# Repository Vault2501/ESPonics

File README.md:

# ESPonics
ESPonics is a ESP32 based automated Aeroponics system. It consists of fan, light and pump control as well as sensors for temperature, humidity, water level, ph and ec and is controlled via a web interface.

# Status
This is still WIP

Done:
* Pump control
* Fan Control
* Light Control
* Test Web UI

Current WIP:
* Sensors
* Case models

Todo:
* Userfriendly UI
* Parameter configuration
* Automatic control
* PCB

# Documentation
Documentation will go to the documentaiton folder

# Media
Photos and Videos of this project can be found here:
* Grow and feeding container with pumps: https://pixel.tchncs.de/i/web/post/594626511061922875
* WIP main controller,sensor and light/fan modules: https://pixel.tchncs.de/i/web/post/594629490395300993
* Finished prototype modules: https://pixel.tchncs.de/i/web/post/597583425622062798
* Video testing the pumps: https://makertube.net/w/gAhuFigTPs9yXAJNz8wZ4G

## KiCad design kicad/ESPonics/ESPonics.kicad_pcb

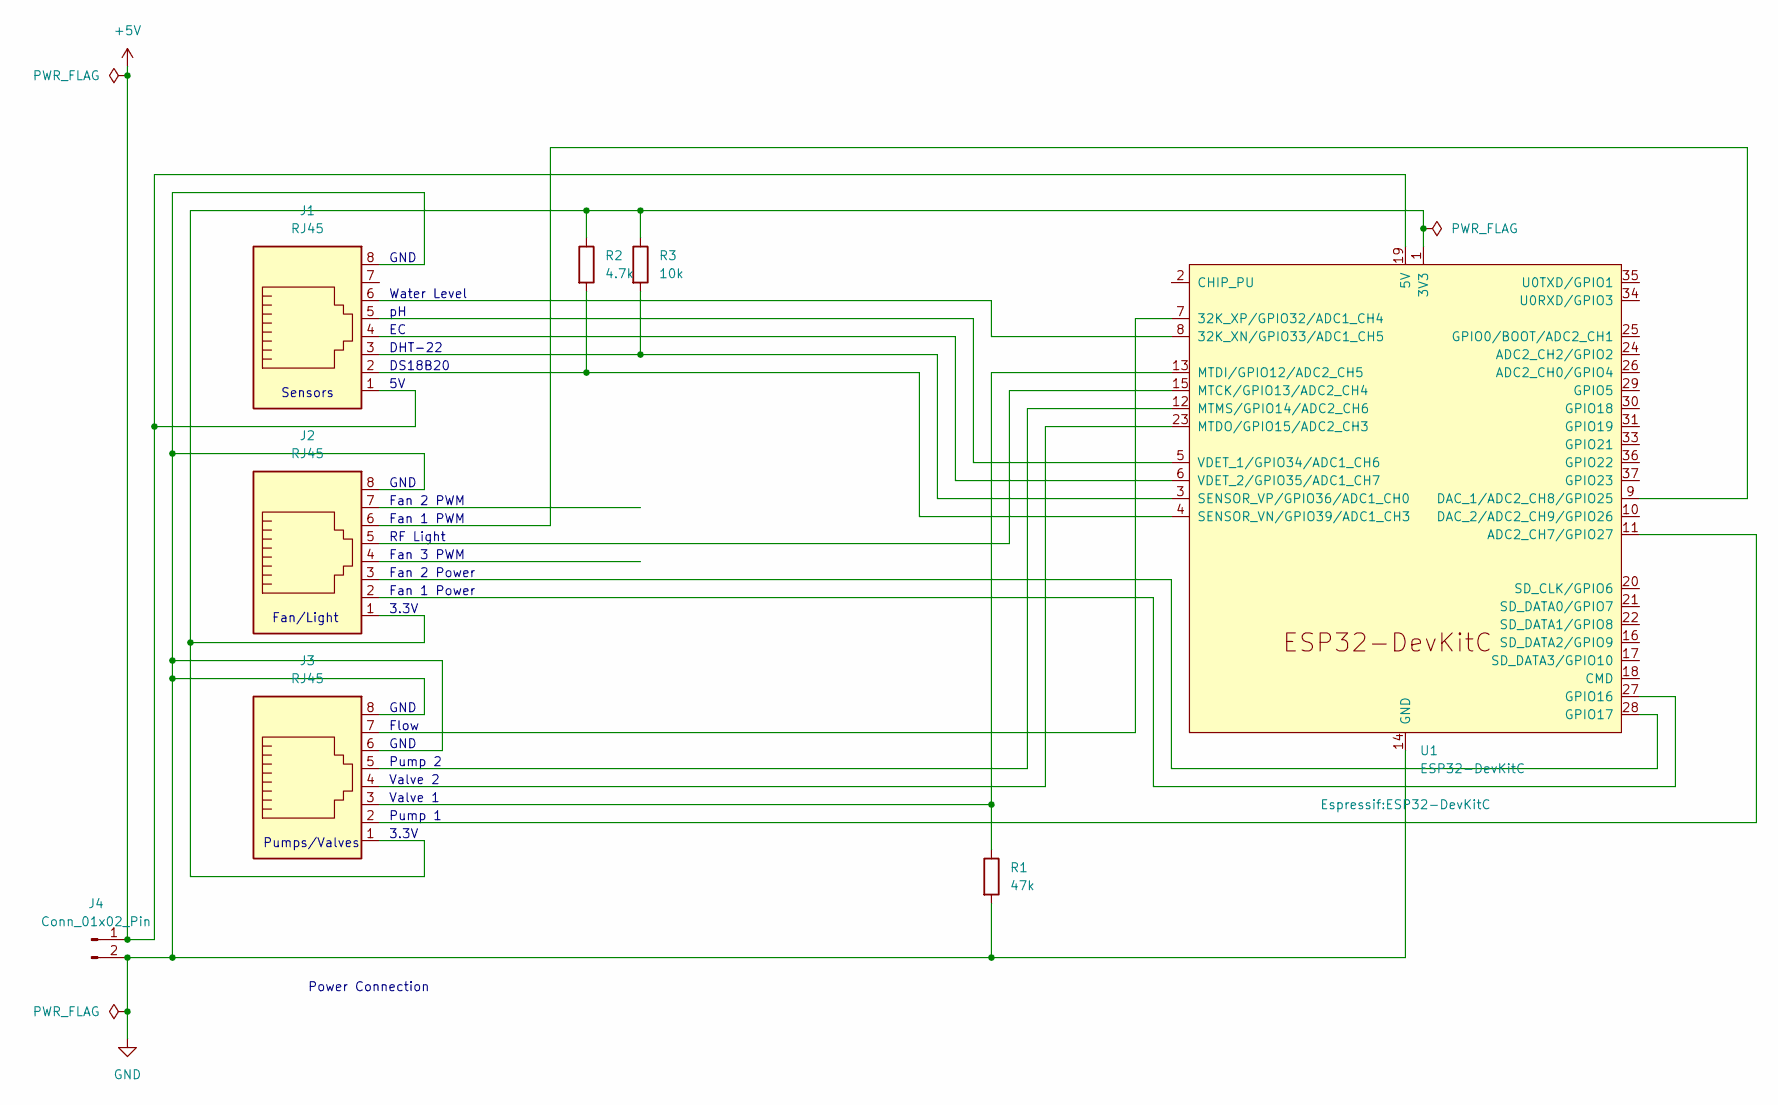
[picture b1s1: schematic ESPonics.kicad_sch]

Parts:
J1, J3: RJ45; RJ45_Amphenol_54602-x08_Horizontal
J2: RJ45
J4: Conn_01x02_Pin; JST_XH_B2B-XH-A_1x02_P2.50mm_Vertical
R1: 47k
R2: 4.7k; R_Axial_DIN0204_L3.6mm_D1.6mm_P1.90mm_Vertical
R3: 10k; R_Axial_DIN0204_L3.6mm_D1.6mm_P1.90mm_Vertical
U1: ESP32-DevKitC

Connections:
+5V: J1.1, J4.1, U1.19 (5V)
GND: J1.8, J2.8, J3.6, J3.8, J4.2, R1.2, U1.14 (GND), U1.32 (GND), U1.38 (GND)
unnamed: J2.1, J3.1, R2.1, R3.1, U1.1 (3V3)
unnamed: J1.6, U1.8 (32K_XN/GPIO33/ADC1_CH5)
unnamed: J3.7, U1.7 (32K_XP/GPIO32/ADC1_CH4)
unnamed: J3.2, U1.11 (ADC2_CH7/GPIO27)
unnamed: J2.6, U1.9 (DAC_1/ADC2_CH8/GPIO25)
unnamed: J2.2, U1.27 (GPIO16)
unnamed: J2.3, U1.28 (GPIO17)
unnamed: J2.5, U1.15 (MTCK/GPIO13/ADC2_CH4)
unnamed: J3.3, R1.1, U1.13 (MTDI/GPIO12/ADC2_CH5)
unnamed: J3.4, U1.23 (MTDO/GPIO15/ADC2_CH3)
unnamed: J3.5, U1.12 (MTMS/GPIO14/ADC2_CH6)
unnamed: J1.2, R2.2, U1.4 (SENSOR_VN/GPIO39/ADC1_CH3)
unnamed: J1.3, R3.2, U1.3 (SENSOR_VP/GPIO36/ADC1_CH0)
unnamed: J1.5, U1.5 (VDET_1/GPIO34/ADC1_CH6)
unnamed: J1.4, U1.6 (VDET_2/GPIO35/ADC1_CH7)

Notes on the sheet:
GND
3.3V
DHT-22
Flow
Valve 1
Fan 2 Power
Pump 1
Valve 2
Fan/Light
Power Connection
Water Level
RF Light
Fan 1 Power
Fan 3 PWM
DS18B20
Fan 1 PWM
Pump 2
Fan 2 PWM
Sensors
Pumps/Valves

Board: 2 copper layers, 8 parts (0 on the bottom side), 17 nets, no tracks yet.

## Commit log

2023-07-23 Initial commit - pumps, valves and flow meter works via ws
2023-07-23 Add index.html and wifi.h
2023-07-23 Add light and fan on/off functionality to to arduino code
2023-07-24 Fix typo, add some debug info and make fans and light switch work
2023-07-25 Add Speed control for Fan1 to webUI - still untested
2023-07-25 Add functionality for setting light times - untested
2023-07-25 Fix typo
2023-08-19 Set light to seconds for testing and fix pwm control for fan
2023-08-19 Add openscad case models and stl files
2023-08-19 Add fan adapter openscad model and stl file
2023-08-19 Add filter openscad model and stl files
2023-08-19 Add clip bar and clip openscad model and stl files
2023-08-20 Add first kicad files
2023-08-20 Add .gitignore
2023-08-20 Add bom template
2023-08-20 Add Sensor GPIO definitions
2023-08-20 Add GPIO connections to kicad
2023-08-20 Added openscad-libraries submodule to the project.
2023-08-20 Add main controller case
2023-08-22 Fix the ethernet port fix
2023-08-22 Add dht reder code
2023-08-22 Add temperature reading code
2023-08-22 Add water state sensor reading code
2023-08-22 Update openscad lib module
2023-08-22 Move global variables to separate file
2023-08-23 Create tabs for UI
2023-08-23 Add pull up resistors
2023-08-24 Enlarge usb access opening in main case
2023-08-24 Add calibration subpage
2023-08-24 Add calibration subpage to code
2023-08-24 Start creating first pcb
2023-08-26 Small pcb changes
2023-08-26 Add stl files for 80mm fan adapter and small fixes for openscad model
2023-08-26 Create generic readSensor function
2023-08-26 Fix typos
2023-08-27 Add debug print for easier handling
2023-08-27 Update schematic with new GPIOs
2023-08-27 Add DHT sensor values to ui
2023-08-27 Add remaining sensor data display to ui and mock ph and ec functions
2023-08-27 Change UI title and headline to ESPonics
2023-08-31 Fix water level code and change connected pins.
2023-09-03 Add first calibration code
2023-09-03 Add playground with experiments
2023-09-03 Add more ph functionality
2023-09-03 Use A0 (G39) for ph sensor
2023-09-03 Remove separate calibration page and finish up ph calibration
2023-09-04 Fix seom ph calibration issues
2023-09-04 Adjust pin assignments
2023-09-04 Another pin fix
2023-09-08 Update kicad file
2023-09-08 Clean up formatting
2023-10-03 Add small connector for alu profile bars
2024-04-23 Add wip bom and overview to docs
2024-05-06 Add delay between turning on pump and opening valve
2024-05-06 Cleanup and added comments to variables
2024-05-06 move wifi credentials
2024-05-06 directly use APKEY and remove const vars
2024-05-06 Move wifimanager functions to separate file
2024-05-07 Remove OTA as it does not work
2024-05-07 Start separating static vars into config file and use symbols for them
2024-05-07 Move variables to structures for better overview
2024-05-07 Continue moving vars to structs
2024-05-07 Move ph settings to structs
2024-05-07 Move pin setup to external function
2024-05-09 Create class for ph sensor
2024-05-10 Add tds class
2024-05-10 Make use of ph classe and remove old code
2024-05-12 Add TDS calibration method
2024-05-12 Clean up variables, add debug routines
2024-05-12 Change ph update code
2024-05-12 Cleanup
2024-05-12 Save calibration parameters
2024-05-12 Move sensor read functions to own file and clean up some more
2024-05-12 fix small issues
2024-05-13 Add schematics for fans and light extension
2024-05-14 Add kicad schema for sensors module
2024-05-15 Add pump and valve module schematics
2024-05-15 Add kicad backup folders to gitignore
2024-05-15 Add power converter to pump module schematic
2024-05-16 Add media for documentation
2024-05-17 Read sensors without passing by reference
2024-05-17 Add debug statements to tds
2024-05-17 Small changes to schematics
2024-05-23 Add calibration values to ui and temp compensation for tds
2024-05-23 Add flow variables to structs
2024-08-23 Add new ph code
2024-08-25 Change ph calibration to detect value and prepare for logging
2024-08-25 Add logging tab to webpage and display log messages on it
2024-08-26 Clean up calibration frontend and add log messages to calibration
2024-08-27 Adjust ph range
2024-08-29 Add OTA functionality
2024-08-30 Add time and day functionality
2024-08-30 Add small scripts to easy create html file for edits
2024-08-31 Clean up CSS
2024-08-31 Display date and time in the ui
2024-08-31 Fix bug
2024-08-31 Fix date and time retrieval
2024-08-31 Adjust timezone and small fix
2024-09-04 Create helper file and put setup functions there, fix small issues
2024-09-05 Clean up flow sensor count and store totalflow regulary
2024-10-31 Add Flow calibration functionality
